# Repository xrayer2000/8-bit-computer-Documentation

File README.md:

# LICENSE

## README

This project is licensed under the Creative Commons Attribution-NonCommercial 4.0 International License (CC BY-NC 4.0).

You are free to:
- Share (copy and redistribute the material in any medium or format)
- Adapt (remix, transform, and build upon the material)

Under the conditions that:
- You must give appropriate credit.
- You may not use the material for commercial purposes.

For full license details, see:  
[https://creativecommons.org/licenses/by-nc/4.0/](https://creativecommons.org/licenses/by-nc/4.0/)

---

## Creative Commons Attribution-NonCommercial 4.0 International (CC BY-NC 4.0)

Copyright (c) 2025 Emil

You are free to:
- Share — copy and redistribute the material in any medium or format
- Adapt — remix, transform, and build upon the material

Under the following terms:
- **Attribution** — You must give appropriate credit, provide a link to the license, and indicate if changes were made.
- **NonCommercial** — You may not use the material for commercial purposes.

No additional restrictions — You may not apply legal terms or technological measures that restrict others from doing anything the license permits.

Full license text:  
[https://creativecommons.org/licenses/by-nc/4.0/legalcode](https://creativecommons.org/licenses/by-nc/4.0/legalcode)

---

## How to attribute

If you use or adapt this project, please include the following attribution:

> “Project name” by Emil is licensed under CC BY-NC 4.0.  
> [https://creativecommons.org/licenses/by-nc/4.0/](https://creativecommons.org/licenses/by-nc/4.0/)

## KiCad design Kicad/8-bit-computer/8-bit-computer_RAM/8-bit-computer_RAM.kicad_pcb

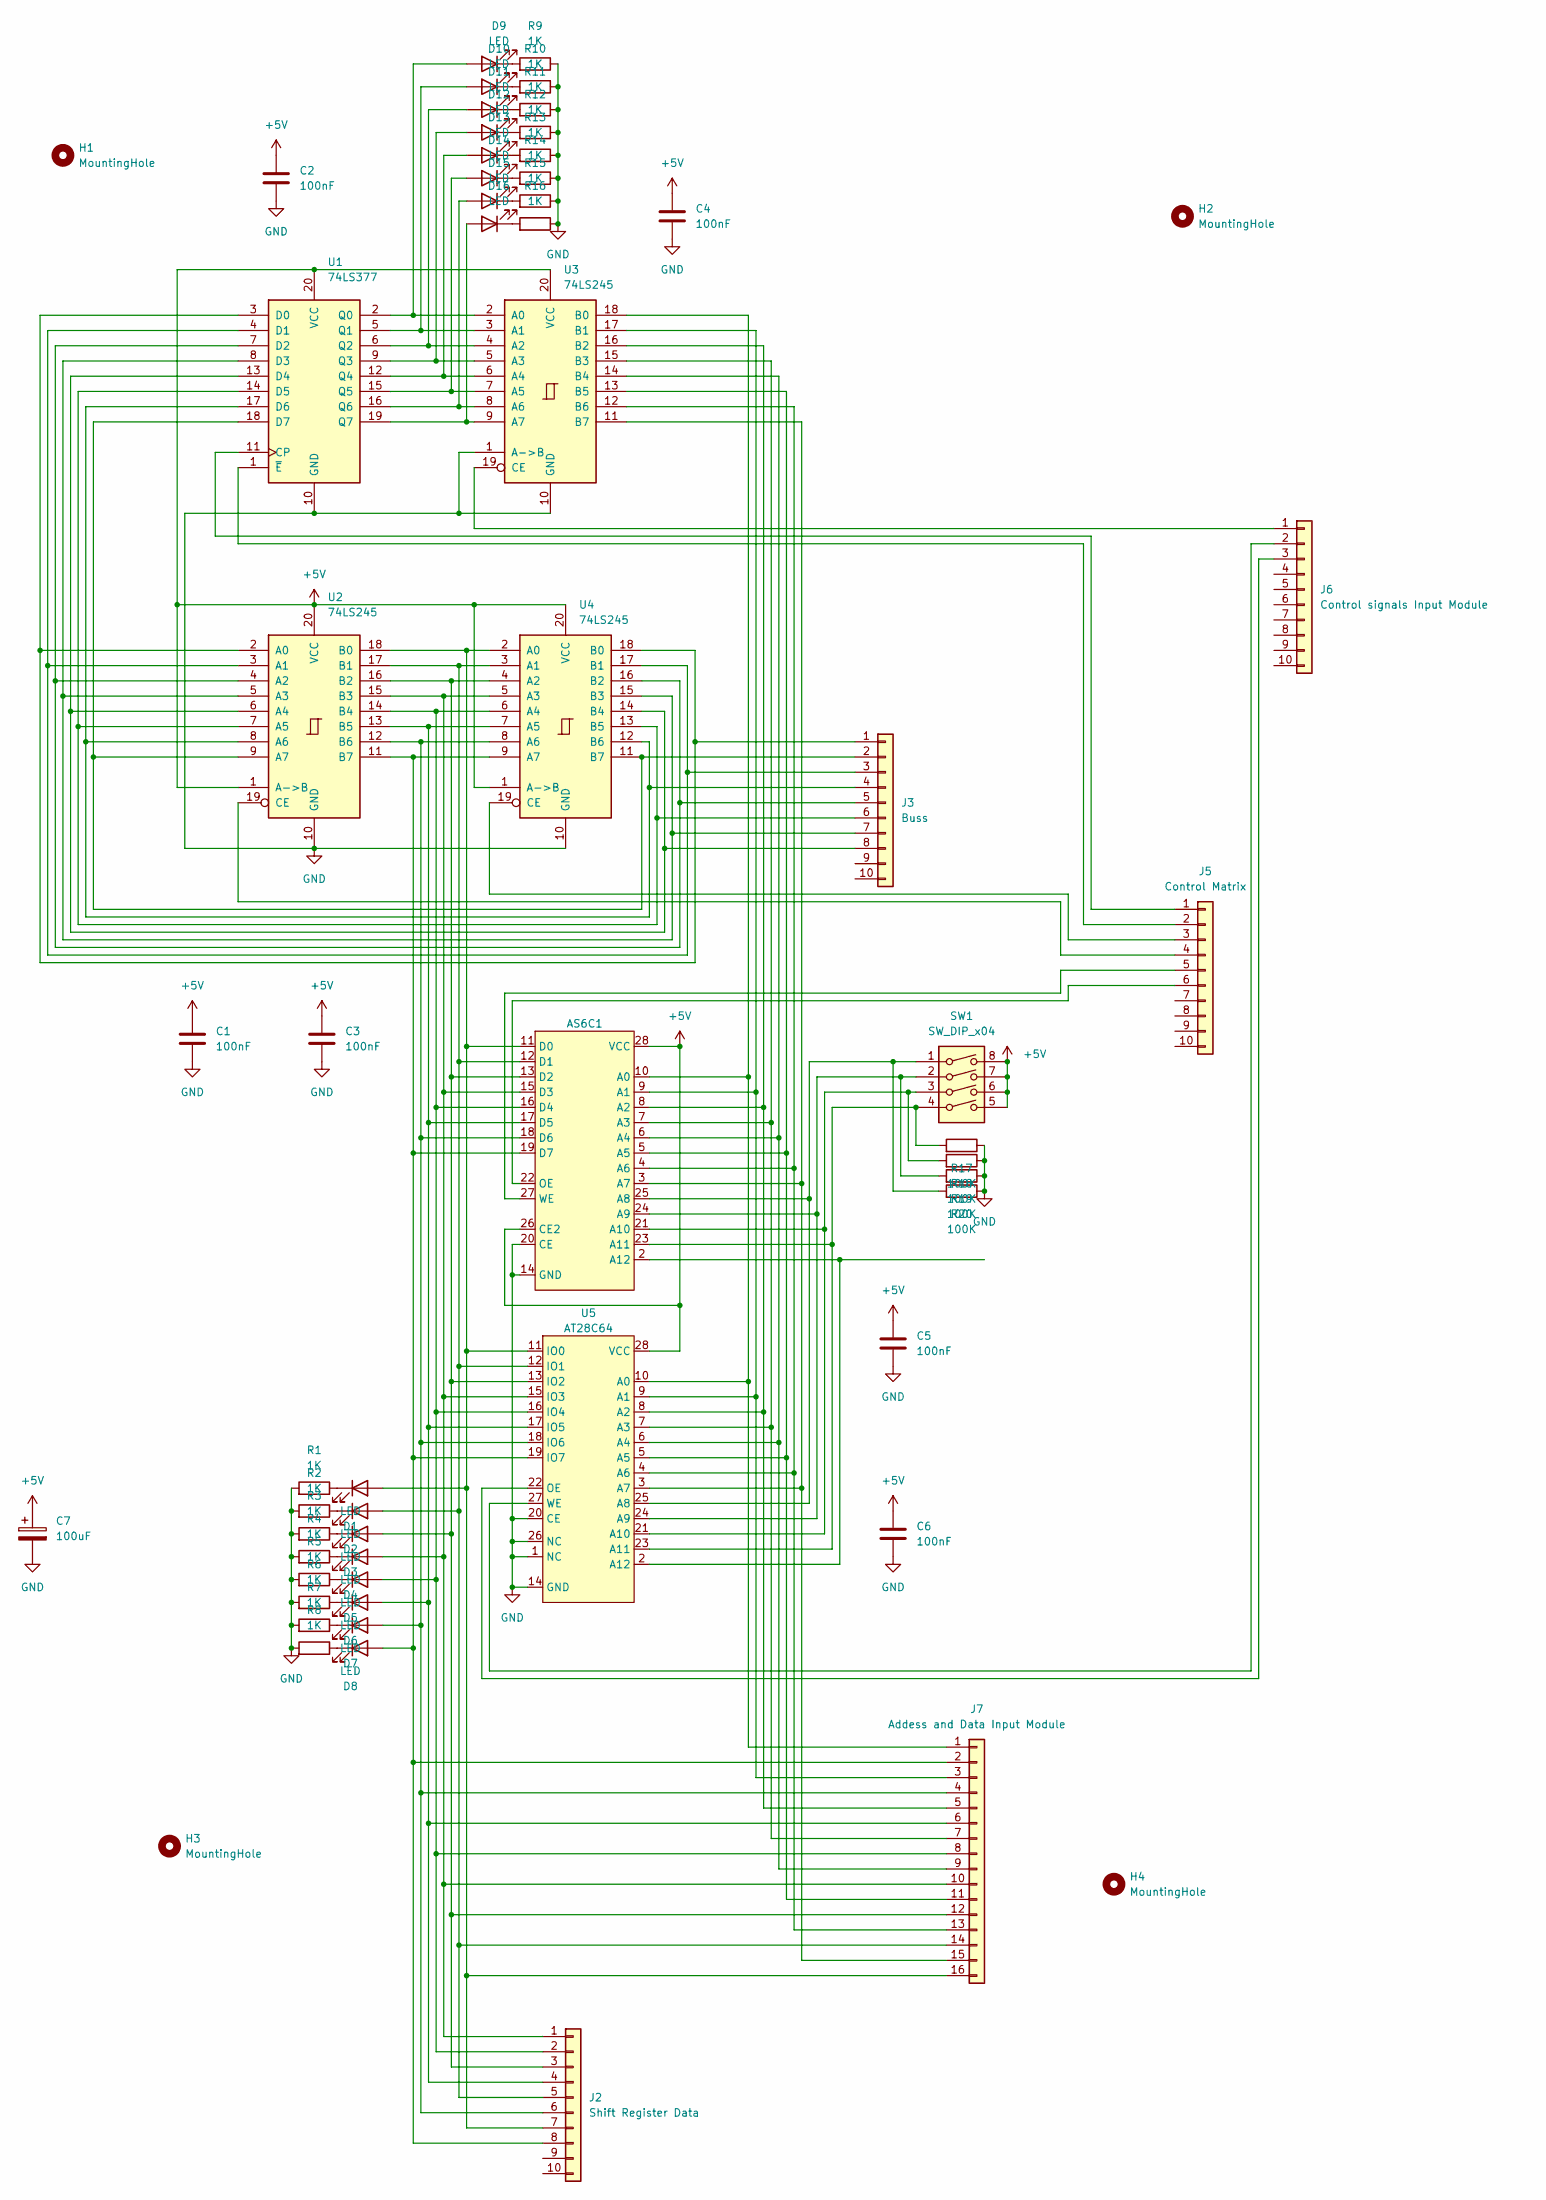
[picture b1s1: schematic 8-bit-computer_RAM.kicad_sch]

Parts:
AS6C1: DIP-28_W15.24mm_Socket
C1, C2, C3, C4, C5, C6: 100nF; C_Disc_D3.0mm_W1.6mm_P2.50mm
C7: 100uF; CP_Radial_D4.0mm_P2.00mm
D1, D2, D3, D4, D5, D6, D7, D8, D9, D10, D11, D12, D13, D14, D15, D16: LED; LED_D3.0mm
H1, H2, H3, H4: MountingHole; MountingHole_3.2mm_M3_DIN965_Pad
J2: Shift Register Data; IDC-Header_2x05_P2.54mm_Vertical
J3: Buss; IDC-Header_2x05_P2.54mm_Vertical
J5: Control Matrix; IDC-Header_2x05_P2.54mm_Vertical
J6: Control signals Input Module; IDC-Header_2x05_P2.54mm_Vertical
J7: Addess and Data Input Module; IDC-Header_2x08_P2.54mm_Vertical
R1, R2, R3, R4, R5, R6, R7, R8, R9, R10, R11, R12, R13, R14, R15, R16: 1K; R_Axial_DIN0207_L6.3mm_D2.5mm_P7.62mm_Horizontal
R17, R18, R19, R20: 100K; R_Axial_DIN0207_L6.3mm_D2.5mm_P7.62mm_Horizontal
SW1: SW_DIP_x04; SW_DIP_SPSTx04_Slide_9.78x12.34mm_W7.62mm_P2.54mm
U1: 74LS377; DIP-20_W7.62mm_Socket
U2, U3, U4: 74LS245; DIP-20_W7.62mm_Socket
U5: AT28C64; DIP-28_W15.24mm_Socket

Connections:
+5V: AS6C1.26 (CE2), AS6C1.28 (VCC), C1.1, C2.1, C3.1, C4.1, C5.1, C6.1, C7.1, SW1.5, SW1.6, SW1.7, SW1.8, U1.20 (VCC), U2.1 (A->B), U2.20 (VCC), U3.20 (VCC), U4.1 (A->B), U4.20 (VCC), U5.28 (VCC)
GND: AS6C1.14 (GND), AS6C1.20 (CE), C1.2, C2.2, C3.2, C4.2, C5.2, C6.2, C7.2, R1.2, R2.2, R3.2, R4.2, R5.2, R6.2, R7.2, R8.2, R9.1, R10.1, R11.1, R12.1, R13.1, R14.1, R15.1, R16.1, R17.1, R18.1, R19.1, R20.1, U1.10 (GND), U2.10 (GND), U3.1 (A->B), U3.10 (GND), U4.10 (GND), U5.1 (NC), U5.14 (GND), U5.20 (CE), U5.26 (NC)
unnamed: AS6C1.10 (A0), J7.1, U3.18 (B0), U5.10 (A0)
unnamed: AS6C1.9 (A1), J7.3, U3.17 (B1), U5.9 (A1)
unnamed: AS6C1.8 (A2), J7.5, U3.16 (B2), U5.8 (A2)
unnamed: AS6C1.7 (A3), J7.7, U3.15 (B3), U5.7 (A3)
unnamed: AS6C1.6 (A4), J7.9, U3.14 (B4), U5.6 (A4)
unnamed: AS6C1.5 (A5), J7.11, U3.13 (B5), U5.5 (A5)
unnamed: AS6C1.4 (A6), J7.13, U3.12 (B6), U5.4 (A6)
unnamed: AS6C1.3 (A7), J7.15, U3.11 (B7), U5.3 (A7)
unnamed: AS6C1.25 (A8), R20.2, SW1.1, U5.25 (A8)
unnamed: AS6C1.24 (A9), R19.2, SW1.2, U5.24 (A9)
unnamed: AS6C1.21 (A10), R18.2, SW1.3, U5.21 (A10)
unnamed: AS6C1.23 (A11), R17.2, SW1.4, U5.23 (A11)
unnamed: AS6C1.2 (A12), U5.2 (A12)
unnamed: AS6C1.11 (D0), D1.2 (A), J2.7, J7.16, U2.18 (B0), U4.2 (A0), U5.11 (IO0)
unnamed: AS6C1.12 (D1), D2.2 (A), J2.5, J7.14, U2.17 (B1), U4.3 (A1), U5.12 (IO1)
unnamed: AS6C1.13 (D2), D3.2 (A), J2.3, J7.12, U2.16 (B2), U4.4 (A2), U5.13 (IO2)
unnamed: AS6C1.15 (D3), D4.2 (A), J2.1, J7.10, U2.15 (B3), U4.5 (A3), U5.15 (IO3)
unnamed: AS6C1.16 (D4), D5.2 (A), J2.2, J7.8, U2.14 (B4), U4.6 (A4), U5.16 (IO4)
unnamed: AS6C1.17 (D5), D6.2 (A), J2.4, J7.6, U2.13 (B5), U4.7 (A5), U5.17 (IO5)
unnamed: AS6C1.18 (D6), D7.2 (A), J2.6, J7.4, U2.12 (B6), U4.8 (A6), U5.18 (IO6)
unnamed: AS6C1.19 (D7), D8.2 (A), J2.8, J7.2, U2.11 (B7), U4.9 (A7), U5.19 (IO7)
unnamed: AS6C1.22 (OE), J5.6
unnamed: AS6C1.27 (WE), J5.5
unnamed: D1.1 (K), R1.1
unnamed: D2.1 (K), R2.1
unnamed: D3.1 (K), R3.1
unnamed: D4.1 (K), R4.1
unnamed: D5.1 (K), R5.1
unnamed: D6.1 (K), R6.1
unnamed: D7.1 (K), R7.1
unnamed: D8.1 (K), R8.1
unnamed: D9.2 (A), U1.2 (Q0), U3.2 (A0)
unnamed: D9.1 (K), R9.2
unnamed: D10.2 (A), U1.5 (Q1), U3.3 (A1)
unnamed: D10.1 (K), R10.2
unnamed: D11.2 (A), U1.6 (Q2), U3.4 (A2)
unnamed: D11.1 (K), R11.2
unnamed: D12.2 (A), U1.9 (Q3), U3.5 (A3)
unnamed: D12.1 (K), R12.2
unnamed: D13.2 (A), U1.12 (Q4), U3.6 (A4)
unnamed: D13.1 (K), R13.2
unnamed: D14.2 (A), U1.15 (Q5), U3.7 (A5)
unnamed: D14.1 (K), R14.2
unnamed: D15.2 (A), U1.16 (Q6), U3.8 (A6)
unnamed: D15.1 (K), R15.2
unnamed: D16.2 (A), U1.19 (Q7), U3.9 (A7)
unnamed: D16.1 (K), R16.2
unnamed: J3.1, U1.3 (D0), U2.2 (A0), U4.18 (B0)
unnamed: J3.2, U1.18 (D7), U2.9 (A7), U4.11 (B7)
unnamed: J3.3, U1.4 (D1), U2.3 (A1), U4.17 (B1)
unnamed: J3.4, U1.17 (D6), U2.8 (A6), U4.12 (B6)
unnamed: J3.5, U1.7 (D2), U2.4 (A2), U4.16 (B2)
unnamed: J3.6, U1.14 (D5), U2.7 (A5), U4.13 (B5)
unnamed: J3.7, U1.8 (D3), U2.5 (A3), U4.15 (B3)
unnamed: J3.8, U1.13 (D4), U2.6 (A4), U4.14 (B4)
unnamed: J5.1, U1.11 (CP)
unnamed: J5.2, U1.1 (~E)
unnamed: J5.3, U4.19 (CE)
unnamed: J5.4, U2.19 (CE)
unnamed: J6.1, U3.19 (CE)
unnamed: J6.2, U5.27 (WE)
unnamed: J6.3, U5.22 (OE)

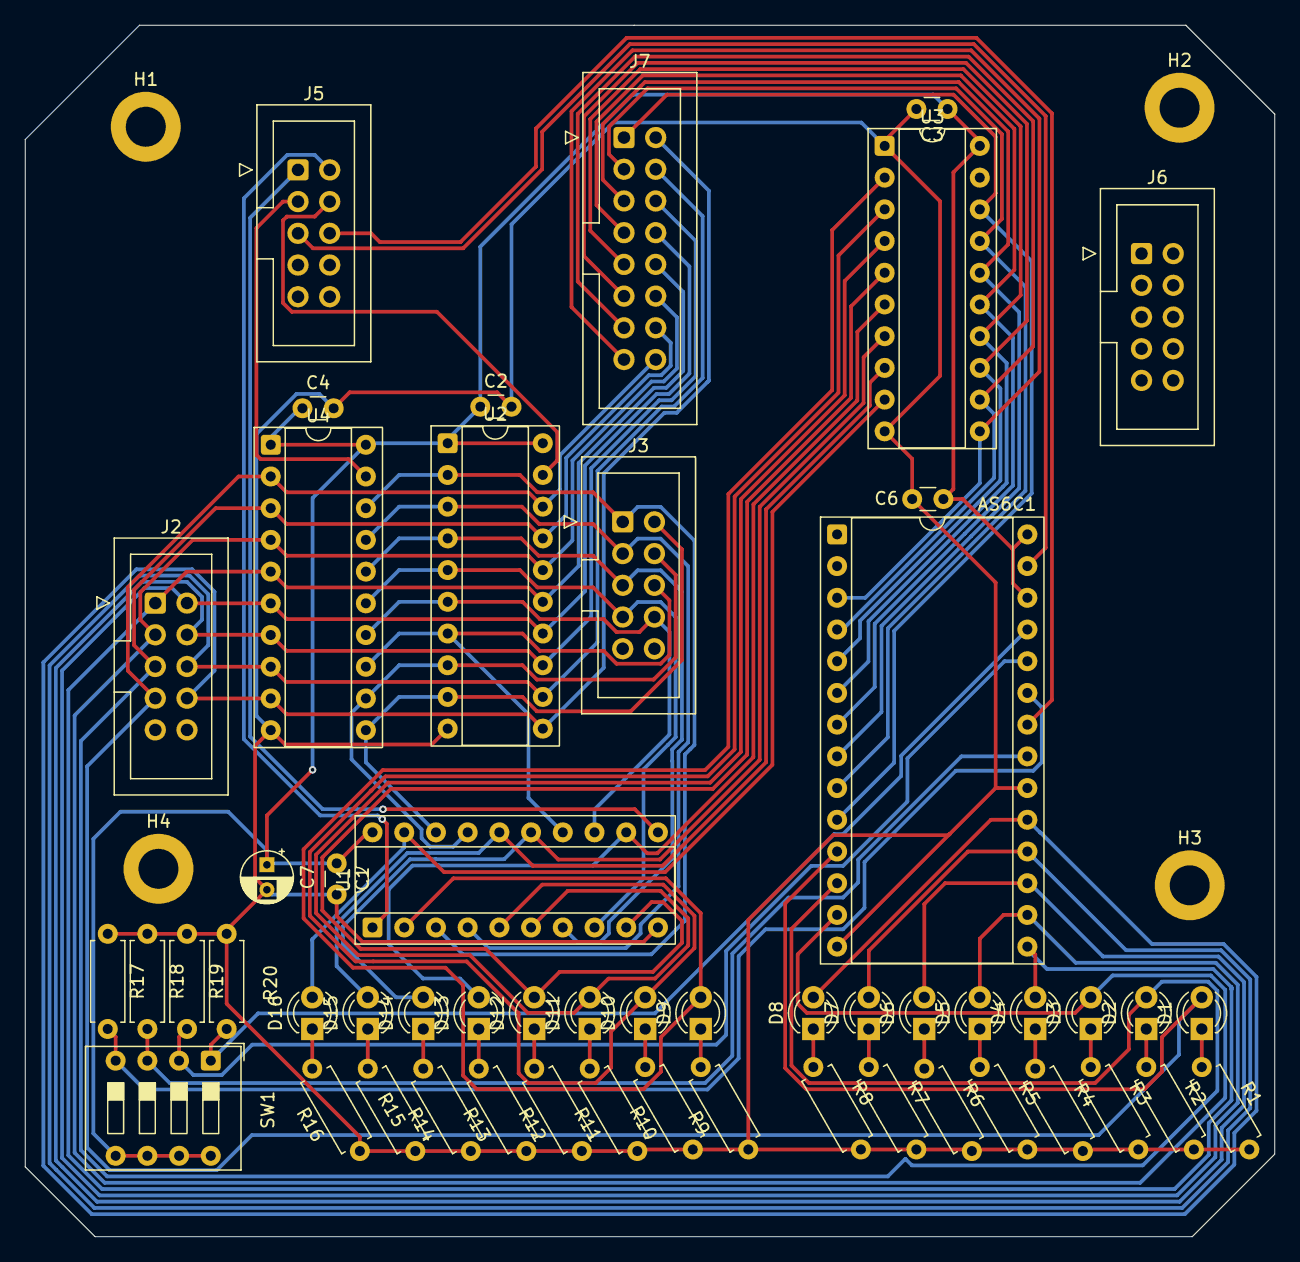
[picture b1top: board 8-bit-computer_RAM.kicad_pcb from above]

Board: 2 copper layers, 100.1 x 97.0 mm, 57 parts (0 on the bottom side), 61 nets.

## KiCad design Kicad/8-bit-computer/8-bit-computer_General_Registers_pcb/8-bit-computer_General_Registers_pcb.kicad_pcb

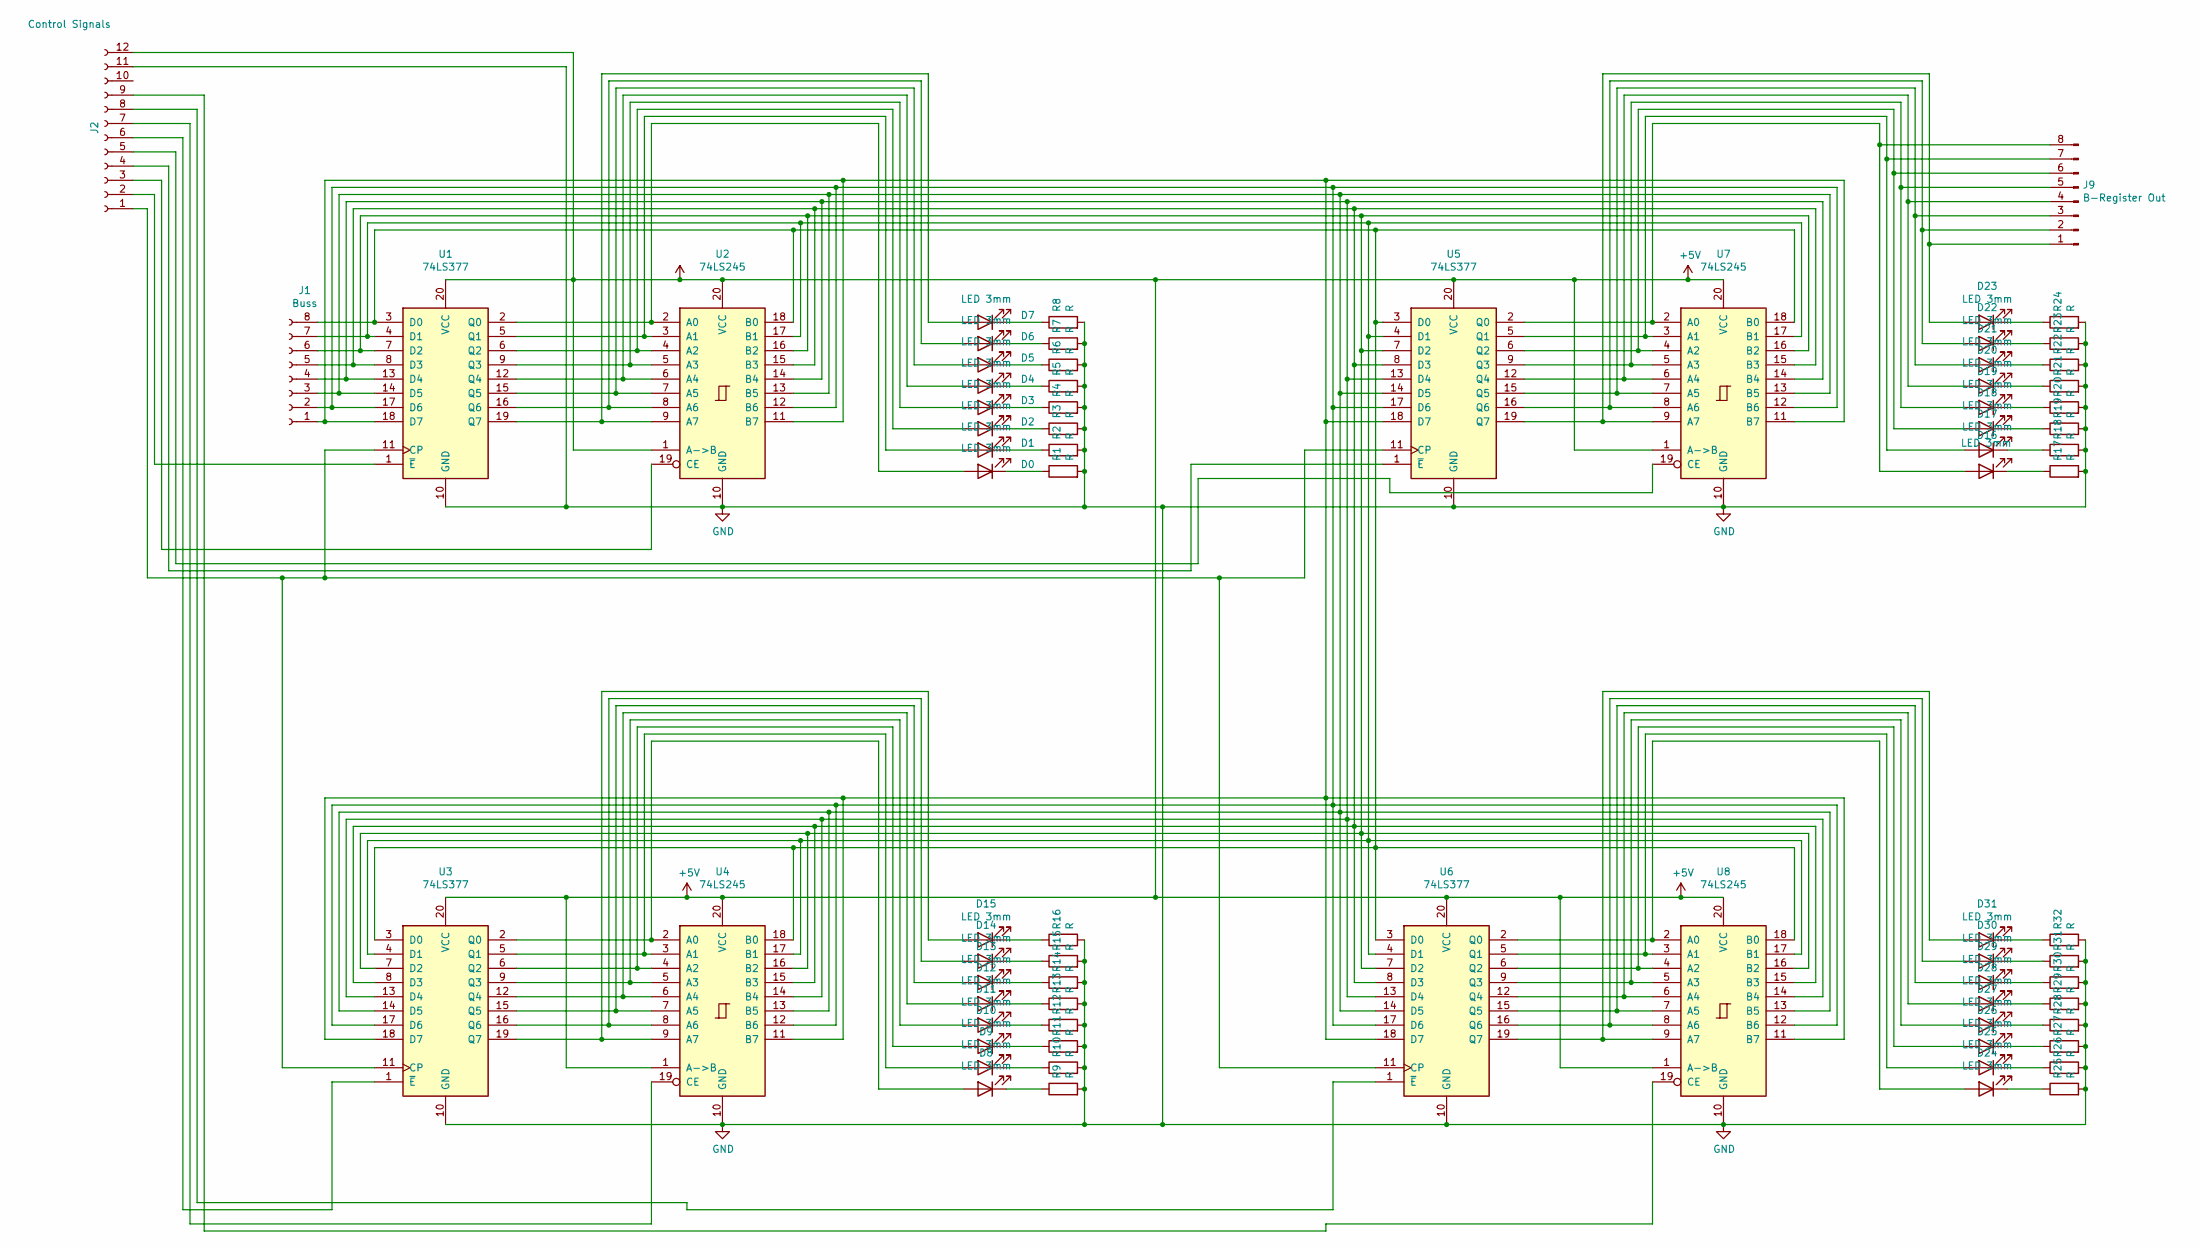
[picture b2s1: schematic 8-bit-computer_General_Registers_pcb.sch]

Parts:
D0, D1, D2, D3, D4, D5, D6, D7, D8, D9, D10, D11, D12, D13, D14, D15, D16, D17, D18, D19, D20, D21, D22, D23, D24, D25, D26, D27, D28, D29, D30, D31: LED 3mm; LED_D3.0mm
J1: Buss; IDC-Header_2x04_P2.54mm_Vertical
J2: Control Signals; IDC-Header_2x06_P2.54mm_Vertical
J9: B-Register Out; IDC-Header_2x04_P2.54mm_Vertical
R1, R2, R3, R4, R5, R6, R7, R8, R9, R10, R11, R12, R13, R14, R15, R16, R17, R18, R19, R20, R21, R22, R23, R24, R25, R26, R27, R28, R29, R30, R31, R32: R; R_Axial_DIN0204_L3.6mm_D1.6mm_P7.62mm_Horizontal
U1, U3, U5, U6: 74LS377; DIP-20_W7.62mm
U2, U4, U7, U8: 74LS245; DIP-20_W7.62mm

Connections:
+5V: J2.12, U1.20 (VCC), U2.1 (A->B), U2.20 (VCC), U3.20 (VCC), U4.1 (A->B), U4.20 (VCC), U5.20 (VCC), U6.20 (VCC), U7.1 (A->B), U7.20 (VCC), U8.1 (A->B), U8.20 (VCC)
GND: J2.11, R1.2, R2.2, R3.2, R4.2, R5.2, R6.2, R7.2, R8.2, R9.2, R10.2, R11.2, R12.2, R13.2, R14.2, R15.2, R16.2, R17.2, R18.2, R19.2, R20.2, R21.2, R22.2, R23.2, R24.2, R25.2, R26.2, R27.2, R28.2, R29.2, R30.2, R31.2, R32.2, U1.10 (GND), U2.10 (GND), U3.10 (GND), U4.10 (GND), U5.10 (GND), U6.10 (GND), U7.10 (GND), U8.10 (GND)
unnamed: D0.1 (K), R1.1
unnamed: D0.2 (A), U1.2 (Q0), U2.2 (A0)
unnamed: D1.1 (K), R2.1
unnamed: D1.2 (A), U1.5 (Q1), U2.3 (A1)
unnamed: D2.1 (K), R3.1
unnamed: D2.2 (A), U1.6 (Q2), U2.4 (A2)
unnamed: D3.1 (K), R4.1
unnamed: D3.2 (A), U1.9 (Q3), U2.5 (A3)
unnamed: D4.1 (K), R5.1
unnamed: D4.2 (A), U1.12 (Q4), U2.6 (A4)
unnamed: D5.1 (K), R6.1
unnamed: D5.2 (A), U1.15 (Q5), U2.7 (A5)
unnamed: D6.1 (K), R7.1
unnamed: D6.2 (A), U1.16 (Q6), U2.8 (A6)
unnamed: D7.1 (K), R8.1
unnamed: D7.2 (A), U1.19 (Q7), U2.9 (A7)
unnamed: D8.1 (K), R9.1
unnamed: D8.2 (A), U3.2 (Q0), U4.2 (A0)
unnamed: D9.1 (K), R10.1
unnamed: D9.2 (A), U3.5 (Q1), U4.3 (A1)
unnamed: D10.1 (K), R11.1
unnamed: D10.2 (A), U3.6 (Q2), U4.4 (A2)
unnamed: D11.1 (K), R12.1
unnamed: D11.2 (A), U3.9 (Q3), U4.5 (A3)
unnamed: D12.1 (K), R13.1
unnamed: D12.2 (A), U3.12 (Q4), U4.6 (A4)
unnamed: D13.1 (K), R14.1
unnamed: D13.2 (A), U3.15 (Q5), U4.7 (A5)
unnamed: D14.1 (K), R15.1
unnamed: D14.2 (A), U3.16 (Q6), U4.8 (A6)
unnamed: D15.1 (K), R16.1
unnamed: D15.2 (A), U3.19 (Q7), U4.9 (A7)
unnamed: D16.1 (K), R17.1
unnamed: D16.2 (A), J9.8, U5.2 (Q0), U7.2 (A0)
unnamed: D17.1 (K), R18.1
unnamed: D17.2 (A), J9.7, U5.5 (Q1), U7.3 (A1)
unnamed: D18.1 (K), R19.1
unnamed: D18.2 (A), J9.6, U5.6 (Q2), U7.4 (A2)
unnamed: D19.1 (K), R20.1
unnamed: D19.2 (A), J9.5, U5.9 (Q3), U7.5 (A3)
unnamed: D20.1 (K), R21.1
unnamed: D20.2 (A), J9.4, U5.12 (Q4), U7.6 (A4)
unnamed: D21.1 (K), R22.1
unnamed: D21.2 (A), J9.3, U5.15 (Q5), U7.7 (A5)
unnamed: D22.1 (K), R23.1
unnamed: D22.2 (A), J9.2, U5.16 (Q6), U7.8 (A6)
unnamed: D23.1 (K), R24.1
unnamed: D23.2 (A), J9.1, U5.19 (Q7), U7.9 (A7)
unnamed: D24.1 (K), R25.1
unnamed: D24.2 (A), U6.2 (Q0), U8.2 (A0)
unnamed: D25.1 (K), R26.1
unnamed: D25.2 (A), U6.5 (Q1), U8.3 (A1)
unnamed: D26.1 (K), R27.1
unnamed: D26.2 (A), U6.6 (Q2), U8.4 (A2)
unnamed: D27.1 (K), R28.1
unnamed: D27.2 (A), U6.9 (Q3), U8.5 (A3)
unnamed: D28.1 (K), R29.1
unnamed: D28.2 (A), U6.12 (Q4), U8.6 (A4)
unnamed: D29.1 (K), R30.1
unnamed: D29.2 (A), U6.15 (Q5), U8.7 (A5)
unnamed: D30.1 (K), R31.1
unnamed: D30.2 (A), U6.16 (Q6), U8.8 (A6)
unnamed: D31.1 (K), R32.1
unnamed: D31.2 (A), U6.19 (Q7), U8.9 (A7)
unnamed: J1.1, U1.18 (D7), U2.11 (B7), U3.18 (D7), U4.11 (B7), U5.18 (D7), U6.18 (D7), U7.11 (B7), U8.11 (B7)
unnamed: J1.2, U1.17 (D6), U2.12 (B6), U3.17 (D6), U4.12 (B6), U5.17 (D6), U6.17 (D6), U7.12 (B6), U8.12 (B6)
unnamed: J1.3, U1.14 (D5), U2.13 (B5), U3.14 (D5), U4.13 (B5), U5.14 (D5), U6.14 (D5), U7.13 (B5), U8.13 (B5)
unnamed: J1.4, U1.13 (D4), U2.14 (B4), U3.13 (D4), U4.14 (B4), U5.13 (D4), U6.13 (D4), U7.14 (B4), U8.14 (B4)
unnamed: J1.5, U1.8 (D3), U2.15 (B3), U3.8 (D3), U4.15 (B3), U5.8 (D3), U6.8 (D3), U7.15 (B3), U8.15 (B3)
unnamed: J1.6, U1.7 (D2), U2.16 (B2), U3.7 (D2), U4.16 (B2), U5.7 (D2), U6.7 (D2), U7.16 (B2), U8.16 (B2)
unnamed: J1.7, U1.4 (D1), U2.17 (B1), U3.4 (D1), U4.17 (B1), U5.4 (D1), U6.4 (D1), U7.17 (B1), U8.17 (B1)
unnamed: J1.8, U1.3 (D0), U2.18 (B0), U3.3 (D0), U4.18 (B0), U5.3 (D0), U6.3 (D0), U7.18 (B0), U8.18 (B0)
unnamed: J2.1, U1.11 (CP), U3.11 (CP), U5.11 (CP), U6.11 (CP)
unnamed: J2.2, U1.1 (~E)
unnamed: J2.3, U2.19 (CE)
unnamed: J2.4, U5.1 (~E)
unnamed: J2.5, U7.19 (CE)
unnamed: J2.6, U3.1 (~E)
unnamed: J2.7, U4.19 (CE)
unnamed: J2.8, U6.1 (~E)
unnamed: J2.9, U8.19 (CE)

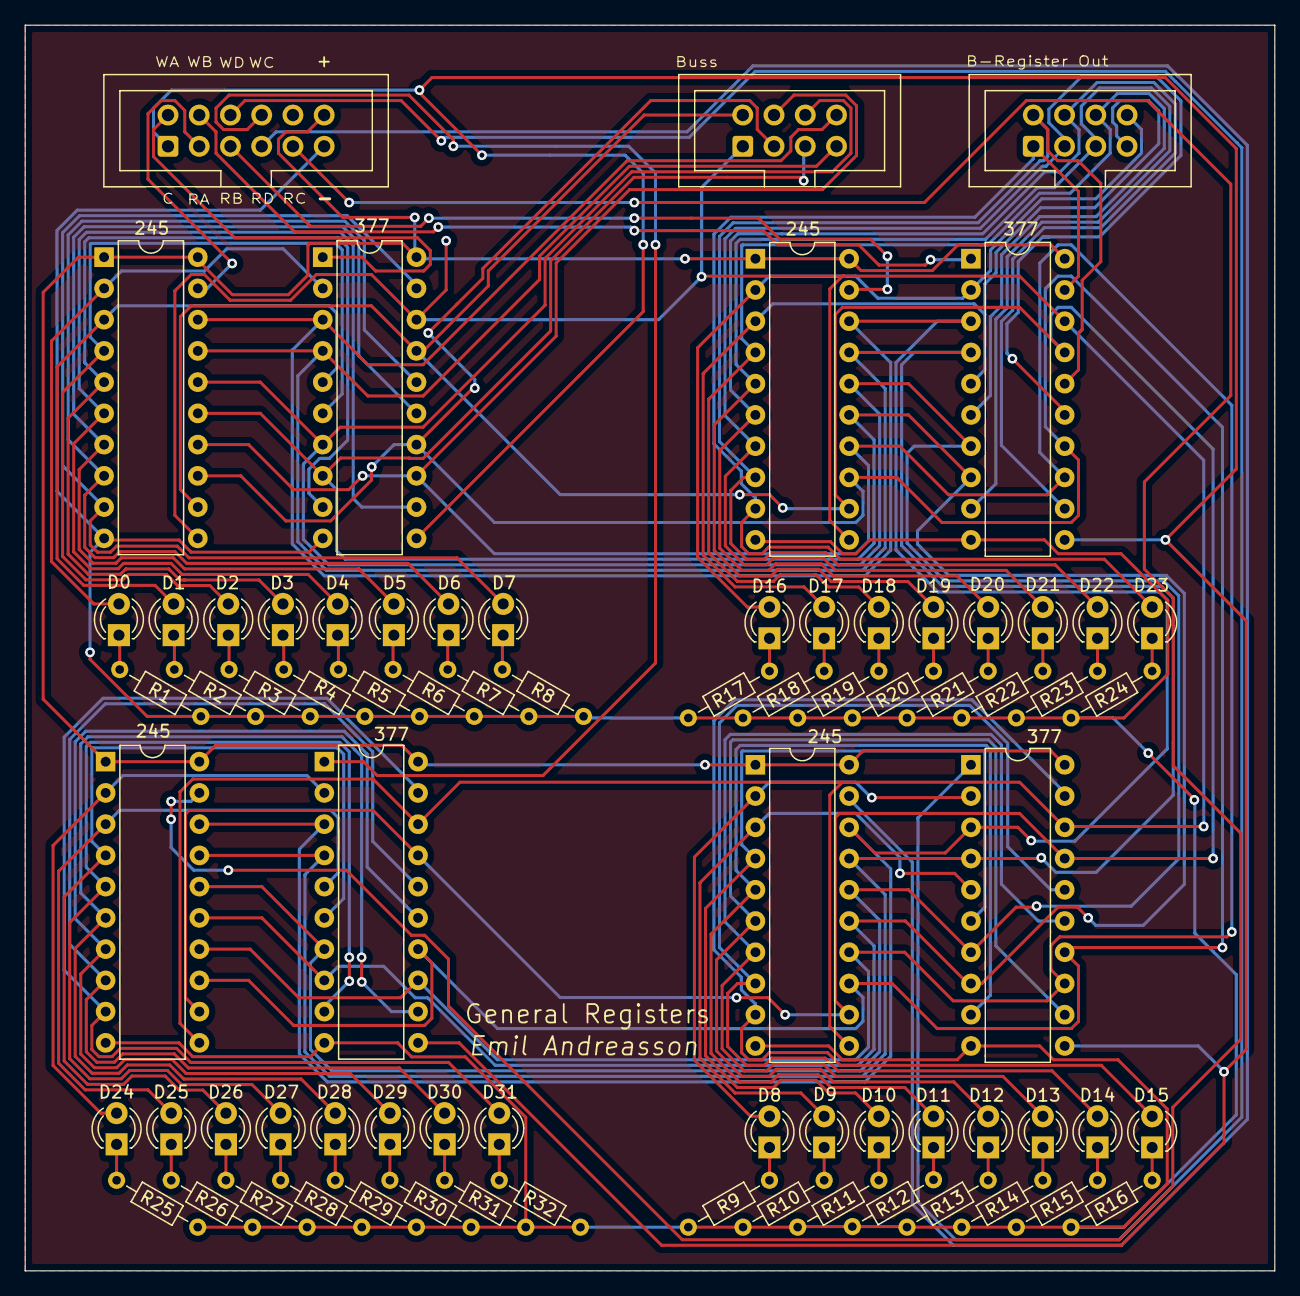
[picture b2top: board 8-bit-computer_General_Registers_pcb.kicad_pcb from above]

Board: 2 copper layers, 101.6 x 101.3 mm, 75 parts (0 on the bottom side), 83 nets.

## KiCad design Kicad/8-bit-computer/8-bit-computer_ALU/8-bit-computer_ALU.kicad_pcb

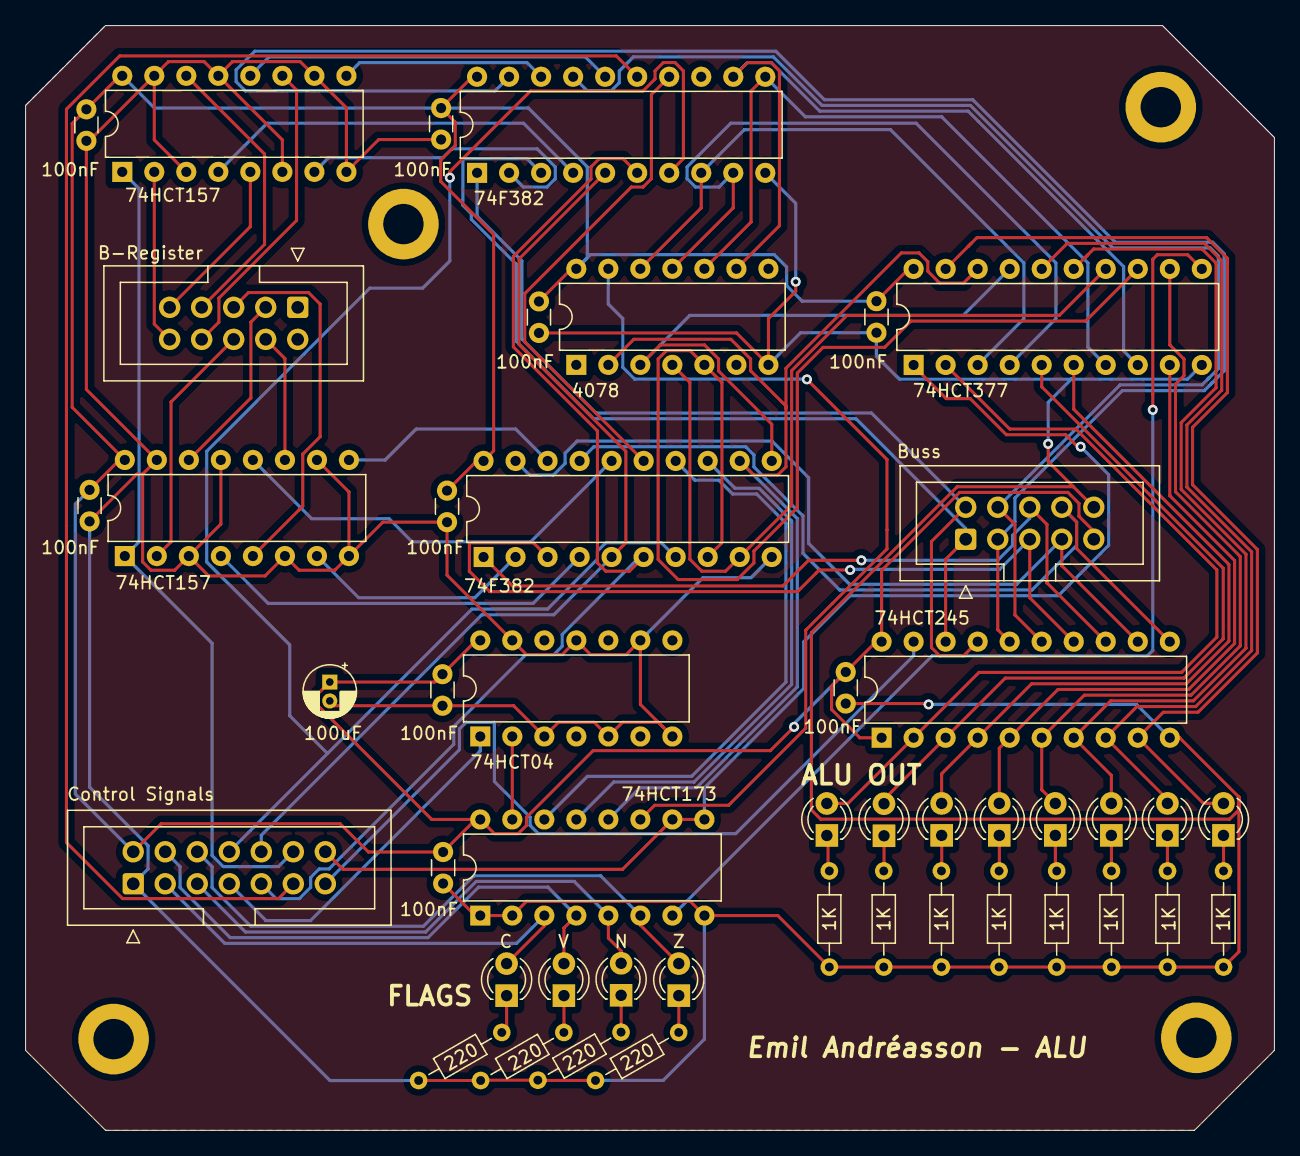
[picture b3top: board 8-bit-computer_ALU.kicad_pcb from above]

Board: 2 copper layers, 99.1 x 87.6 mm, 50 parts (0 on the bottom side), 72 nets.

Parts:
C1: 100uF; CP_Radial_D4.0mm_P1.50mm
C2, C3, C4, C5, C6, C7, C8, C9, C10: 100nF; C_Disc_D3.0mm_W1.6mm_P2.50mm
C11: C; LED_D3.0mm
D1, D2, D3, D4, D5, D6, D7, D8: LED; LED_D3.0mm
H1, H2, H3, H4: MountingHole; MountingHole_3.2mm_M3_DIN965_Pad
J1: Control Signals; IDC-Header_2x07_P2.54mm_Vertical
J2: B-Register; IDC-Header_2x05_P2.54mm_Vertical
J3: Buss; IDC-Header_2x05_P2.54mm_Vertical
N1: N; LED_D3.0mm
R1, R2, R3, R4, R5, R6, R7, R8: 1K; R_Axial_DIN0204_L3.6mm_D1.6mm_P7.62mm_Horizontal
R9, R10, R11, R12: 220; R_Axial_DIN0204_L3.6mm_D1.6mm_P7.62mm_Horizontal
U1: 74HCT04; DIP-14_W7.62mm
U3: 74HCT377; DIP-20_W7.62mm
U4, U5: 74HCT157; DIP-16_W7.62mm
U6: 74HCT245; DIP-20_W7.62mm
U7, U8: 74F382; DIP-20_W7.62mm
U9: 4078; DIP-14_W7.62mm
U10: 74HCT173; DIP-16_W7.62mm
V1: V; LED_D3.0mm
Z1: Z; LED_D3.0mm

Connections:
+5V: C1.1, C2.1, C3.1, C4.1, C5.1, C6.1, C7.1, C8.1, C9.1, C10.1, J1.2, J3.9, U1.14 (VCC), U3.20 (VCC), U4.16 (VCC), U5.16 (VCC), U6.1 (A->B), U6.20 (VCC), U7.20 (5V), U8.20 (5V), U9.14 (Vdd), U10.16 (VCC)
/C: C11.2 (A), J1.3, U10.3 (Q0)
/N: J1.5, N1.2 (A), U10.5 (Q2)
/V: J1.4, U10.4 (Q1), V1.2 (A)
/Z: J1.6, U10.6 (Q3), Z1.2 (A)
GND: C1.2, C2.2, C3.2, C4.2, C5.2, C6.2, C7.2, C8.2, C9.2, C10.2, J1.1, J3.10, R1.1, R2.1, R3.1, R4.1, R5.1, R6.1, R7.1, R8.1, R9.1, R10.1, R11.1, R12.1, U1.3, U1.5, U1.7 (GND), U1.9, U1.11, U1.13, U3.10 (GND), U4.3 (I1a), U4.6 (I1b), U4.8 (GND), U4.10 (I1c), U4.13 (I1d), U4.15 (E), U5.3 (I1a), U5.6 (I1b), U5.8 (GND), U5.10 (I1c), U5.13 (I1d), U5.15 (E), U6.10 (GND), U7.10 (Gnd), U8.10 (Gnd), U9.7 (Vss), U10.1 (Oe1), U10.2 (Oe2), U10.8 (GND)
unnamed: C11.1 (K), R9.2
unnamed: D1.2 (A), U3.2 (Q0), U6.2 (A0)
unnamed: D1.1 (K), R1.2
unnamed: D2.2 (A), U3.5 (Q1), U6.3 (A1)
unnamed: D2.1 (K), R2.2
unnamed: D3.2 (A), U3.6 (Q2), U6.4 (A2)
unnamed: D3.1 (K), R3.2
unnamed: D4.2 (A), U3.9 (Q3), U6.5 (A3)
unnamed: D4.1 (K), R4.2
unnamed: D5.2 (A), U3.12 (Q4), U6.6 (A4)
unnamed: D5.1 (K), R5.2
unnamed: D6.2 (A), U3.15 (Q5), U6.7 (A5)
unnamed: D6.1 (K), R6.2
unnamed: D7.2 (A), U3.16 (Q6), U6.8 (A6)
unnamed: D7.1 (K), R7.2
unnamed: D8.2 (A), U3.19 (Q7), U6.9 (A7)
unnamed: D8.1 (K), R8.2
unnamed: J1.7, U1.1
unnamed: J1.8, U7.7 (S2), U8.7 (S2)
unnamed: J1.9, U7.6 (S1), U8.6 (S1)
unnamed: J1.10, U7.5 (S0), U8.5 (S0)
unnamed: J1.11, U8.15 (Cn)
unnamed: J1.12, U4.1 (S), U5.1 (S)
unnamed: J1.13, U6.19 (CE)
unnamed: J1.14, U3.1 (~E), U10.9 (E1), U10.10 (E2)
unnamed: J2.3, U5.14 (I0d)
unnamed: J2.4, U5.11 (I0c)
unnamed: J2.5, U5.5 (I0b)
unnamed: J2.6, U5.2 (I0a)
unnamed: J2.7, U4.14 (I0d)
unnamed: J2.8, U4.11 (I0c)
unnamed: J2.9, U4.5 (I0b)
unnamed: J2.10, U4.2 (I0a)
unnamed: J3.1, U6.18 (B0), U8.3 (A0)
unnamed: J3.2, U6.17 (B1), U8.1 (A1)
unnamed: J3.3, U6.16 (B2), U8.19 (A2)
unnamed: J3.4, U6.15 (B3), U8.17 (A3)
unnamed: J3.5, U6.14 (B4), U7.3 (A0)
unnamed: J3.6, U6.13 (B5), U7.1 (A1)
unnamed: J3.7, U6.12 (B6), U7.19 (A2)
unnamed: J3.8, U6.11 (B7), U7.17 (A3)
unnamed: N1.1 (K), R11.2
unnamed: U3.3 (D0), U8.8 (F0), U9.12
unnamed: U3.4 (D1), U8.9 (F1), U9.11
unnamed: U3.7 (D2), U8.11 (F2), U9.10
unnamed: U3.8 (D3), U8.12 (F3), U9.9
unnamed: U3.13 (D4), U7.8 (F0), U9.5
unnamed: U3.14 (D5), U7.9 (F1), U9.4
unnamed: U3.17 (D6), U7.11 (F2), U9.3
unnamed: U4.4 (Za), U8.4 (B0)
unnamed: U4.7 (Zb), U8.2 (B1)
unnamed: U4.9 (Zc), U8.18 (B2)
unnamed: U4.12 (Zd), U8.16 (B3)
unnamed: U5.4 (Za), U7.4 (B0)
unnamed: U5.7 (Zb), U7.2 (B1)
unnamed: U5.9 (Zc), U7.18 (B2)
unnamed: U5.12 (Zd), U7.16 (B3)
unnamed: U7.15 (Cn), U8.14 (Cn+4)
unnamed: U3.11 (CP), U10.7 (Cp)
unnamed: U7.14 (Cn+4), U10.14 (D0)
unnamed: U7.13 (OVR), U10.13 (D1)
unnamed: U3.18 (D7), U7.12 (F3), U9.2, U10.12 (D2)
unnamed: U9.13, U10.11 (D3)
unnamed: U1.2, U10.15 (Mr)
unnamed: R10.2, V1.1 (K)
unnamed: R12.2, Z1.1 (K)

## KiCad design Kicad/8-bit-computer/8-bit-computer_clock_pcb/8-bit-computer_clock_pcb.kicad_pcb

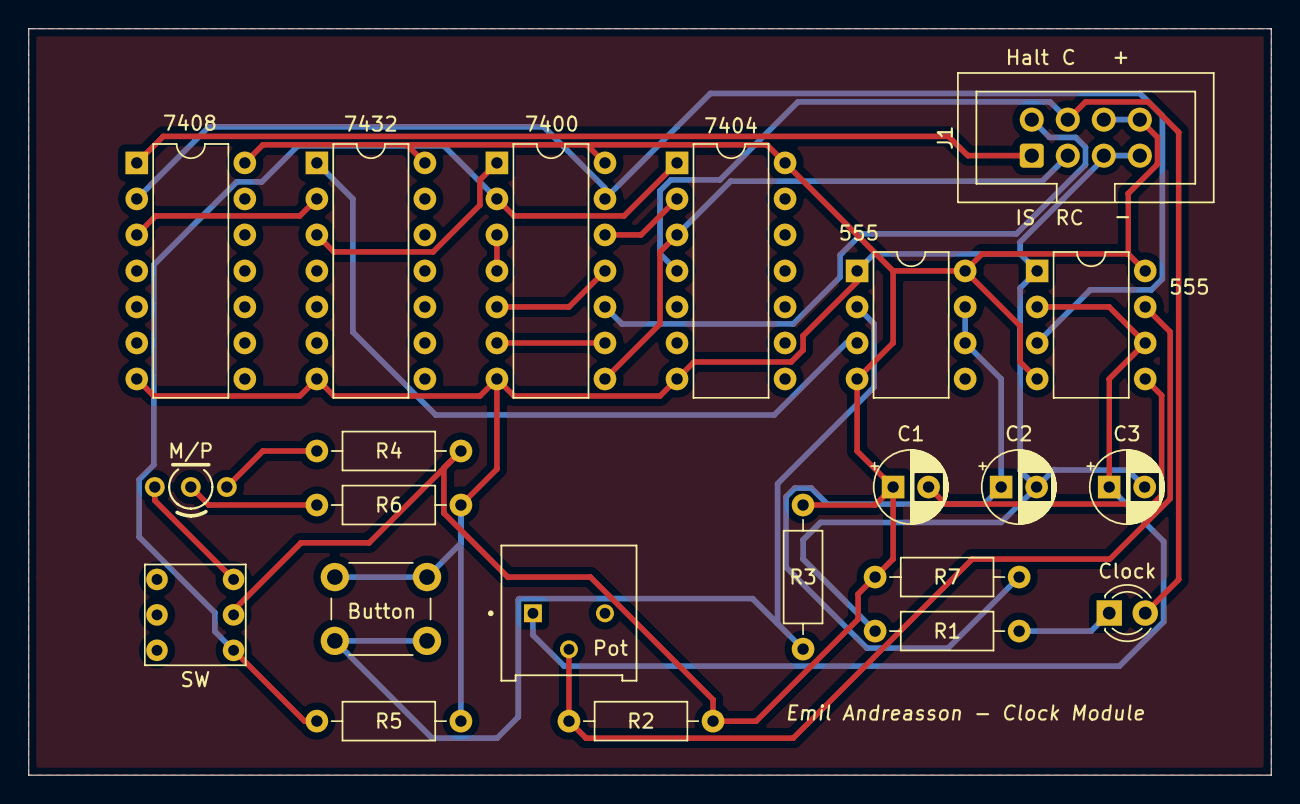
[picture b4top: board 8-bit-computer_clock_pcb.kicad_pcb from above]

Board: 2 copper layers, 87.6 x 52.6 mm, 22 parts (0 on the bottom side), 24 nets.

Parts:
555, 555#2: NE555P; DIP-8_W7.62mm
7400: 74HCT00; DIP-14_W7.62mm
7404: 74HCT04; DIP-14_W7.62mm
7408: 74HCT08; DIP-14_W7.62mm
7432: 74HCT32; DIP-14_W7.62mm
Button: manual clock; SW_PUSH_6mm
C1: 0.1u; CP_Radial_D5.0mm_P2.50mm
C2, C3: 100u; CP_Radial_D5.0mm_P2.50mm
Clock: Clock; LED_D3.0mm_IRBlack
J1: Conn_01x08_Female; IDC-Header_2x04_P2.54mm_Vertical
M/P: L-115WEGW-CA; DUOLED-A-3MM
Pot: R_POT; TRIM_3386P-1-101T
R1: 1.47k; R_Axial_DIN0207_L6.3mm_D2.5mm_P10.16mm_Horizontal
R2: 1k; R_Axial_DIN0207_L6.3mm_D2.5mm_P10.16mm_Horizontal
R3, R5: 100k; R_Axial_DIN0207_L6.3mm_D2.5mm_P10.16mm_Horizontal
R4: 100; R_Axial_DIN0207_L6.3mm_D2.5mm_P10.16mm_Horizontal
R6, R7: 470; R_Axial_DIN0207_L6.3mm_D2.5mm_P10.16mm_Horizontal
SW: SW_SPDT; Switch_on_off

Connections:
+5V: 555.4, 555.8, 555#2.4, 555#2.8, 7400.14, 7404.14, 7408.14, 7432.14, C1.1, J1.6, J1.8, R1.2, R2.2, R3.2, R4.2, SW.2
GND: 555.1, 555#2.1, 7400.7, 7404.7, 7408.7, 7432.7, Button.1, C2.2, C3.2, J1.5, J1.7, R5.2, R6.1, R7.1
unnamed: 555#2.2, Button.2, R3.1
unnamed: 555.5, C1.2
unnamed: 555#2.6, 555#2.7, C2.1, R1.1
unnamed: 555.2, 555.6, C3.1, Pot.1
unnamed: Clock.1, R7.2
unnamed: 7404.4, Clock.2, J1.4
unnamed: 7408.1, J1.1
unnamed: 7400.10, J1.2
unnamed: 7400.8, 7404.3, J1.3
unnamed: M/P.1, SW.1
unnamed: M/P.2, R6.2
unnamed: M/P.3, R4.1
unnamed: 555.7, Pot.2, R2.1
unnamed: 7400.2, 7404.1, R5.1, SW.3
unnamed: 555.3, 7400.13, 7408.2
unnamed: 555#2.3, 7432.1
unnamed: 7408.3, 7432.2
unnamed: 7400.1, 7432.3
unnamed: 7400.3, 7400.4
unnamed: 7400.6, 7400.9
unnamed: 7400.5, 7400.11
unnamed: 7400.12, 7404.2
